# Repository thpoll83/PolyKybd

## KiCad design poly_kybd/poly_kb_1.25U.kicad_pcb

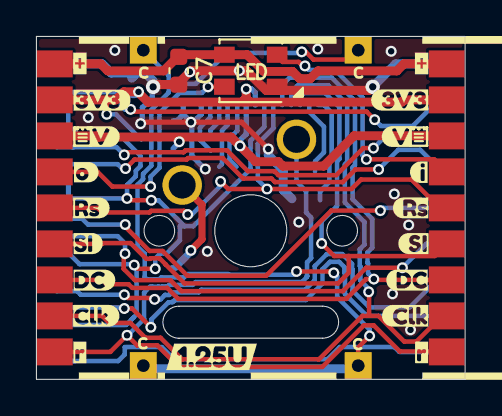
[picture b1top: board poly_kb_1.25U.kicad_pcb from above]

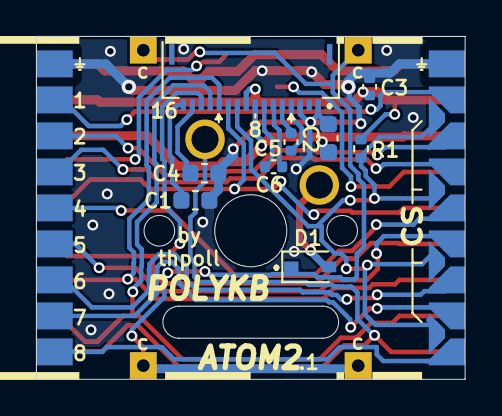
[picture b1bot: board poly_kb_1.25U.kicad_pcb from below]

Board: 2 copper layers, 23.8 x 19.0 mm, 39 parts (11 on the bottom side), 27 nets.

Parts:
C1, C2: 2.2uF; C_0603_1608Metric
C3, C5, C6: 1uF; C_0402_1005Metric
C4: 4.7uF; C_0603_1608Metric
C7: 100nF; C_0603_1608Metric
D1: D_Small; D_SOD-323Ext
J1: Conn_01x16; FPC_16_JUSHUO_AFC05_S16FIA_00
J2: North; TestPoin_1.5x1.5mm_Drill0.7mm
J3: WestFront; AtomConnect2
J4: EastFront; AtomConnect2
J5: WestBack; AtomConnectCS
J6: EastBack; AtomConnect2
J7: South; TestPoin_1.5x1.5mm_Drill0.7mm
J8: North2; TestPoin_1.5x1.5mm_Drill0.7mm
J9: South2; TestPoin_1.5x1.5mm_Drill0.7mm
LED1: WS2812B-Mini
R1: 1M; R_0402_1005Metric
SW1: SW_Push; SW_Cherry_MX_1.00u_PCB_NoSilk
kibuzzard-61EFA8F1: G***; kibuzzard-61EFA8F1
kibuzzard-61EFAA6D: G***; kibuzzard-61EFAA6D
kibuzzard-61EFABBF: G***; kibuzzard-61EFABBF
kibuzzard-61EFACF9: G***; kibuzzard-61EFACF9
kibuzzard-61EFBE2C: G***; kibuzzard-61EFBE2C
kibuzzard-61EFBE3D: G***; kibuzzard-61EFBE3D
kibuzzard-61EFBE21: G***; kibuzzard-61EFBE21
kibuzzard-61EFBE87: G***; kibuzzard-61EFBE87
kibuzzard-61EFD7F9: G***; kibuzzard-61EFD7F9
kibuzzard-61EFD863: G***; kibuzzard-61EFD863
kibuzzard-61EFD879: G***; kibuzzard-61EFD879
kibuzzard-61EFD908, kibuzzard-61EFD908#2: G***; kibuzzard-61EFD908
kibuzzard-61EFD947, kibuzzard-61EFD947#2: G***; kibuzzard-61EFD947
kibuzzard-61EFDAA0: G***; kibuzzard-61EFDAA0
kibuzzard-61EFDAC6: G***; kibuzzard-61EFDAC6
kibuzzard-61EFDAEE: G***; kibuzzard-61EFDAEE
kibuzzard-6209FD7E: G***; kibuzzard-6209FD7E

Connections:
/Keyboard/sheet605ED2EB/3V3: C3.1, J1.9, J3.2, J4.2, R1.1
/Keyboard/sheet605ED2EB/4V2: C2.1, J1.8, J3.3, J4.3
/Keyboard/sheet605ED2EB/5V: C7.1, J3.1, J4.1, LED1.1 (VDD)
/Keyboard/sheet605ED2EB/CS: J1.10, J5.10, R1.2
/Keyboard/sheet605ED2EB/D-C: J1.12, J3.7, J4.7
/Keyboard/sheet605ED2EB/GND: C1.2, C2.2, C3.2, C4.2, C7.2, J1.1, J1.3, J5.1, J6.1, LED1.3 (VSS)
/Keyboard/sheet605ED2EB/KeyCol: D1.1 (K), J2.1, J7.1, J8.1, J9.1
/Keyboard/sheet605ED2EB/KeyRow: J3.9, J4.9, SW1.1
/Keyboard/sheet605ED2EB/LED_DIN: J3.4, J4.4, LED1.2 (DOUT), LED1.4 (DIN)
/Keyboard/sheet605ED2EB/RESET: J1.11, J3.5, J4.5
/Keyboard/sheet605ED2EB/SCLK: J1.13, J3.8, J4.8
/Keyboard/sheet605ED2EB/SDIN: J1.14, J3.6, J4.6
CS1: J5.2, J6.2
CS2: J5.3, J6.3
CS3: J5.4, J6.4
CS4: J5.5, J6.5
CS5: J5.6, J6.6
CS6: J5.7, J6.7
CS7: J5.8, J6.8
CS8: J5.9, J6.9
unnamed: C1.1, J1.16
unnamed: C4.1, J1.15
unnamed: C5.1, J1.4
unnamed: C5.2, J1.5
unnamed: C6.1, J1.6
unnamed: C6.2, J1.7
unnamed: D1.2 (A), SW1.2

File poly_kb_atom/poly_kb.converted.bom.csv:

Designator,Quantity,Value,Footprint,LCSC Part #,Comment
"C1, C2",2,2.2uF,C_0603_1608Metric,C23630," Unpolarized capacitor, small symbol"
"C3, C5, C6",3,1uF,C_0402_1005Metric,C52923," Unpolarized capacitor, small symbol"
C4,1,4.7uF,C_0603_1608Metric,C19666," Unpolarized capacitor, small symbol"
D1,1,D_Small,D_SOD-323F,C2826370," Diode, small symbol"
J1,1,Conn_01x16,FPC_16_JUSHUO_AFC05_S16FIA_00,C561388," Generic connector, single row, 01x16, script generated (kicad-library-utils/schlib/autogen/connector/)"
J2,1,North,TestPoin_1.5x1.5mm_Drill0.7mm,," Generic connector, single row, 01x01, script generated (kicad-library-utils/schlib/autogen/connector/)"
J3,1,WestFront,AtomConnect2,," Generic connector, single row, 01x09, script generated (kicad-library-utils/schlib/autogen/connector/)"
J4,1,EastFront,AtomConnect2,," Generic connector, single row, 01x09, script generated (kicad-library-utils/schlib/autogen/connector/)"
J5,1,WestBack,AtomConnectCS,," Generic connector, single row, 01x10, script generated (kicad-library-utils/schlib/autogen/connector/)"
J6,1,EastBack,AtomConnect2,," Generic connector, single row, 01x09, script generated (kicad-library-utils/schlib/autogen/connector/)"
J7,1,South,TestPoin_1.5x1.5mm_Drill0.7mm,," Generic connector, single row, 01x01, script generated (kicad-library-utils/schlib/autogen/connector/)"
J8,1,North2,TestPoin_1.5x1.5mm_Drill0.7mm,," Generic connector, single row, 01x01, script generated (kicad-library-utils/schlib/autogen/connector/)"
J9,1,South2,TestPoin_1.5x1.5mm_Drill0.7mm,," Generic connector, single row, 01x01, script generated (kicad-library-utils/schlib/autogen/connector/)"
LED1,1,WS2812B-Mini,WS2812B-Mini,C527089, RGB LED with integrated controller
SW1,1,SW_Push,SW_Cherry_MX_1.00u_PCB_NoSilk,," Push button switch, generic, two pins"

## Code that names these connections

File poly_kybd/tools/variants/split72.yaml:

# split72 variant description — the parameter set needed to GENERATE a
# top-level PolyKybd schematic from a KLE layout (see tools/gen_variant_sch.py).
#
# Everything electrical that distinguishes this board lives here; the KLE file
# contributes only geometry + the matrix position of every key. The hand-drawn
# sub-sheets (key cell, buffer, shift registers, MCU) stay the unit of reuse —
# the generator only instantiates and wires them.

name: poly_kybd_split72
kle: layouts/split72.kle.json     # labels are "row,col" (firmware matrix coords)

matrix:
  rows_per_side: 5                # KLE rows 0..4 = left half, 5..9 = right half
  cols: 8

# Matrix positions that exist electrically but have NO key/display cell —
# they are flat symbols on the board (here: the rotary-encoder push button).
matrix_only:
  left: [[3, 7]]
  right: [[8, 0]]

# The per-key cell sheet (switch + keycap OLED + RGB LED, 12-pin interface).
key_cell:
  sheet: SSD1306_TO_SPI.kicad_sch # split42 uses SSD1306_TO_SPI_NO_LED.kicad_sch
  size: [22.86, 33.02]
  # fixed-function cell pins -> shared nets (KeyRow/KeyCol/SCLK/SDIN/CS/LED_*
  # are per-key and derived from the rules below)
  nets: {D-C: D-C, RESET: RESET, GND: GND, VDD: VDD, VSUP: VSUP}

# MCU sheet + complete GPIO contract. col_pins/row_pins order IS the firmware
# MATRIX_COL_PINS / MATRIX_ROW_PINS order (split72/config.h) — Col1..ColN /
# Row1..RowN net names attach in this order.
mcu:
  sheet: rp_pico.kicad_sch
  col_pins: [GP10, GP11, GP12, GP13, GP14, GP15, GP16, GP3]
  row_pins: [GP18, GP19, GP20, GP21, GP22]
  pins:                           # fixed-function GPIOs -> net
    GP0: I2C_SDA                  # Cirque trackpad / LTR-559 bus
    GP1: I2C_SCL
    GP2: LED_ARR_START            # WS2812_DI_PIN — RGB chain entry
    GP4: SERIAL_COM1              # split link (full-duplex pair)
    GP5: SERIAL_COM2
    GP6: SCLK_RAW                 # SPI_SCK  (hand-made routes via series R)
    GP7: SDIN_RAW                 # SPI_MOSI (hand-made routes via series R)
    GP8: D-C                      # SPI_DC_PIN
    GP9: RESET                    # HW_RST_PIN (also the SR MReset)
    GP17: SPI0_CS_NC
    GP23: TB_INT                  # trackpad data-ready
    GP25: ENC_A                   # rotary encoder
    GP29: ENC_B
    GP26: SR_DATA                 # display-select shift registers
    GP27: SR_CLOCK
    GP28: SR_LATCH
  power: {3V3: VDD, GND: GND, VBUS: VBUS, VSYS: VSYS}

# Keycap-OLED data distribution: one ni_buffer2 per chain re-drives
# SCLK_RAW/SDIN_RAW into SCLKn/SDINn. chains maps chain number -> the matrix
# cols (0-based) it serves, per side. 8 columns share 7 chains; WHICH pair of
# columns shares is a per-side board-routing choice (the split72 L/R asymmetry
# that made invert_display()'s `c--` necessary lives in the col->CS rule, not
# here).
buffer:
  sheet: ni_buffer2.kicad_sch
  nets: {A_IN: SDIN_RAW, B_IN: SCLK_RAW, VCC: VDD, GND: GND}
  outputs: {A_OUT: SDIN, B_OUT: SCLK}   # + chain number
chains:
  left:  {1: [0], 2: [1], 3: [2], 4: [3], 5: [4], 6: [5], 7: [6, 7]}
  right: {1: [0, 1], 2: [2], 3: [3], 4: [4], 5: [5], 6: [6], 7: [7]}

# Display-select (CS) contract: key at matrix (r, c) -> shift-register output
# Out{r % rows_per_side + 1}_{bit}. The bit rule reproduces the firmware
# key_display[] indexing (split72.c):
#   left            : bit = c + 1                  (direct)
#   right upper rows: bit = c                      (the invert_display c-- quirk)
#   right bottom row: bit = c + 1                  (direct)
shift_registers:
  sheet: shift_registers.kicad_sch
  count: 5
  nets: {Data: SR_DATA, Clock: SR_CLOCK, Latch: SR_LATCH, MReset: RESET,
         VCC: VDD, GND: GND}
  cs_bit:
    left:  {default: col_plus_1}
    right: {default: col_plus_1, upper_rows: col}

# Per-key RGB chain (WS2812): LED_ARR_START -> first key's LED_DIN, then
# LED_DOUT -> LED_DIN point-to-point. Order rule measured off both hand-made
# boards: rows top-to-bottom, each row in DECREASING matrix column.
led_chain:
  order: [row_asc, col_desc]

# Reference hand-made schematics for --verify (contract comparison; a '?' on
# the hand-made side — a net that disappears into flat symbols the tracer
# can't follow, e.g. series resistors — tolerates any generated value).
reference:
  left: ../poly_kybd_split72_left.kicad_sch
  right: ../poly_kybd_split72_right.kicad_sch
